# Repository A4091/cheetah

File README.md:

# A4770 Cheetah

A modern successor to the A4091 / A4092.

All the goodness of the A4092:
* TSSOP parts for smaller footprint
* SPI Flash instead of parallel EPROM
* CPLD instead of GALs
* Autoconfig moved into CPLD

And also:
* Update to NCR53c770 SCSI Host Controller
* Ultra-Wide SCSI support
* Drop unneeded ferrites and capacitors on SCSI lines
* Replace DIP-switch mechanism entirely w/ Software/Logic
* No more resistor arrays

# THIS IS WORK IN PROGRESS. DO NOT BUILD. FEEDBACK IS WELCOME

<!-- 

And also as a real PCB:

-->

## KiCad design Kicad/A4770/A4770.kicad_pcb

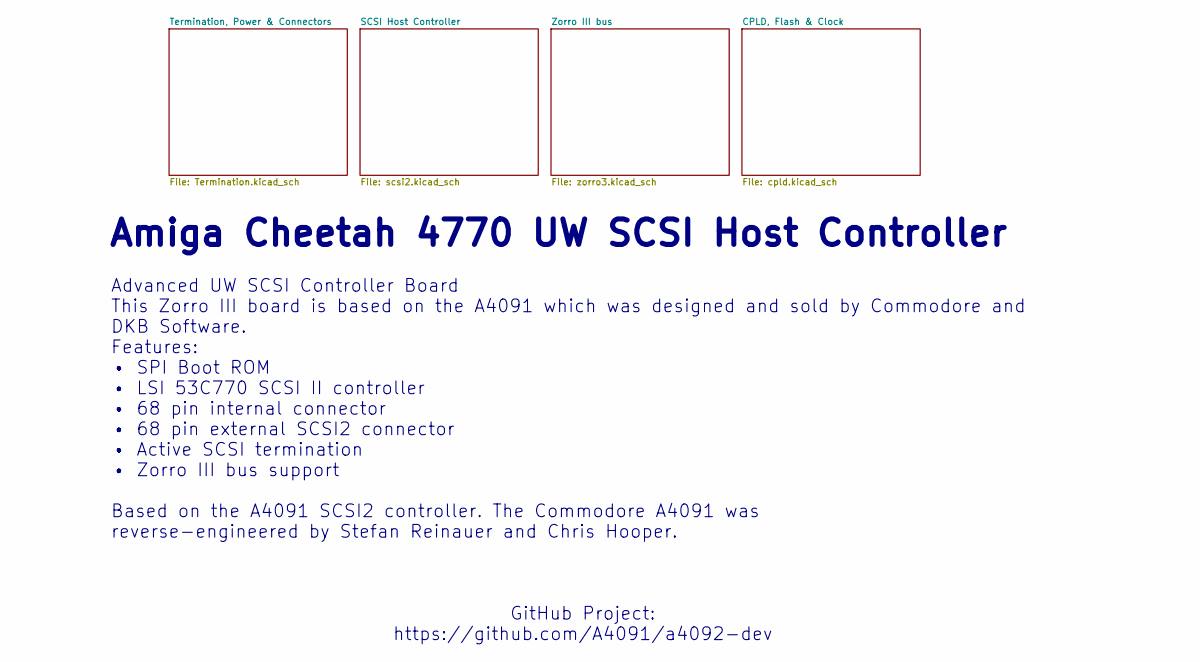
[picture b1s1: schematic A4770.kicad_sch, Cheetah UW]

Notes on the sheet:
Advanced UW SCSI Controller Board This Zorro III board is based on the A4091 which was designed and sold by Commodore and DKB Software. Features: • SPI Boot ROM • LSI 53C770 SCSI II controller • 68 pin internal connector • 68 pin external SCSI2 connector • Active SCSI termination • Zorro III bus su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
GitHub Project: https://github.com/A4091/a4092-dev
Amiga Cheetah 4770 UW SCSI Host Controller

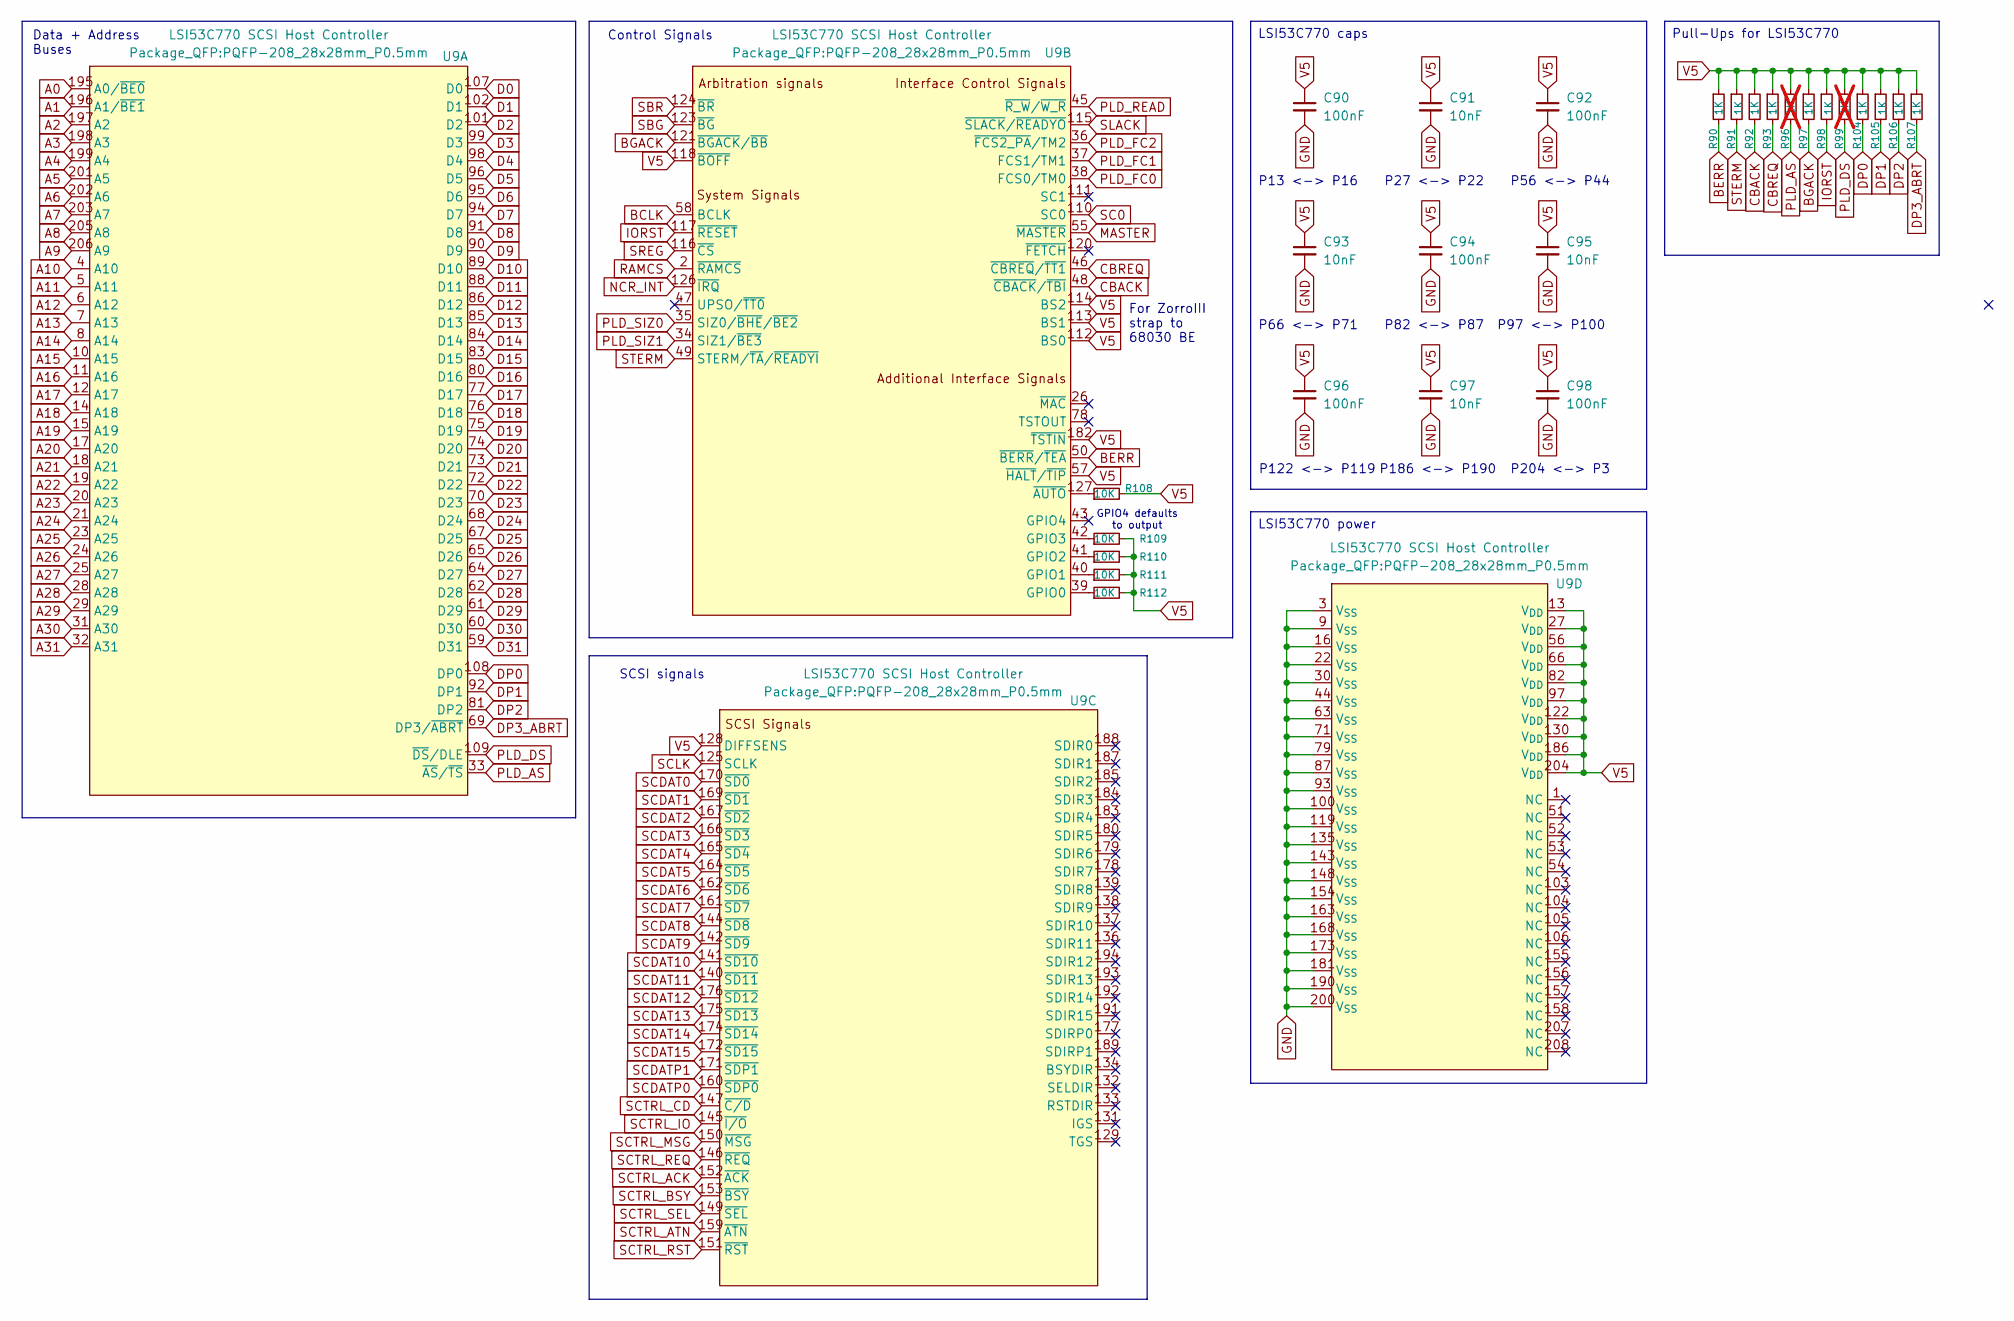
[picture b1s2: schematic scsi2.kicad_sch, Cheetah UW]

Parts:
C90, C92, C94, C96, C98: 100nF; C_0603_1608Metric_Pad1.08x0.95mm_HandSolder; LCSC Part # C14663
C91, C93, C95, C97: 10nF; C_0603_1608Metric_Pad1.08x0.95mm_HandSolder; LCSC Part # C57112
R90, R91, R92, R93, R97, R98, R104, R105, R106, R107: 1K; R_0603_1608Metric_Pad0.98x0.95mm_HandSolder; LCSC Part # C21190
R96, R99: 1K; R_0603_1608Metric_Pad0.98x0.95mm_HandSolder; LCSC Part # C21190; not fitted
R108, R109, R110, R111, R112: 10K; R_0603_1608Metric_Pad0.98x0.95mm_HandSolder; LCSC Part # C25804
U9: LSI53C770 SCSI Host Controller; PQFP-208_28x28mm_P0.5mm; LCSC Part # C9900193416

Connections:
A0: U9.195 (A0/~BE0); also elsewhere on the board
A1: U9.196 (A1/~BE1); also elsewhere on the board
A2: U9.197 (A2); also elsewhere on the board
A3: U9.198 (A3); also elsewhere on the board
A4: U9.199 (A4); also elsewhere on the board
A5: U9.201 (A5); also elsewhere on the board
A6: U9.202 (A6); also elsewhere on the board
A7: U9.203 (A7); also elsewhere on the board
A8: U9.205 (A8); also elsewhere on the board
A9: U9.206 (A9); also elsewhere on the board
A10: U9.4 (A10); also elsewhere on the board
A11: U9.5 (A11); also elsewhere on the board
A12: U9.6 (A12); also elsewhere on the board
A13: U9.7 (A13); also elsewhere on the board
A14: U9.8 (A14); also elsewhere on the board
A15: U9.10 (A15); also elsewhere on the board
A16: U9.11 (A16); also elsewhere on the board
A17: U9.12 (A17); also elsewhere on the board
A18: U9.14 (A18); also elsewhere on the board
A19: U9.15 (A19); also elsewhere on the board
A20: U9.17 (A20); also elsewhere on the board
A21: U9.18 (A21); also elsewhere on the board
A22: U9.19 (A22); also elsewhere on the board
A23: U9.20 (A23); also elsewhere on the board
A24: U9.21 (A24); also elsewhere on the board
A25: U9.23 (A25); also elsewhere on the board
A26: U9.24 (A26); also elsewhere on the board
A27: U9.25 (A27); also elsewhere on the board
A28: U9.28 (A28); also elsewhere on the board
A29: U9.29 (A29); also elsewhere on the board
A30: U9.31 (A30); also elsewhere on the board
A31: U9.32 (A31); also elsewhere on the board
BCLK: U9.58 (BCLK); also elsewhere on the board
BERR: R90.2, U9.50 (~BERR/~TEA); also elsewhere on the board
BGACK: R97.2, U9.121 (~BGACK/~BB)
CBACK: R92.2, U9.48 (~CBACK/~TBI); also elsewhere on the board
CBREQ: R93.2, U9.46 (~CBREQ/~TT1); also elsewhere on the board
D0: U9.107 (D0); also elsewhere on the board
D1: U9.102 (D1); also elsewhere on the board
D2: U9.101 (D2); also elsewhere on the board
D3: U9.99 (D3); also elsewhere on the board
D4: U9.98 (D4); also elsewhere on the board
D5: U9.96 (D5); also elsewhere on the board
D6: U9.95 (D6); also elsewhere on the board
D7: U9.94 (D7); also elsewhere on the board
D8: U9.91 (D8); also elsewhere on the board
D9: U9.90 (D9); also elsewhere on the board
D10: U9.89 (D10); also elsewhere on the board
D11: U9.88 (D11); also elsewhere on the board
D12: U9.86 (D12); also elsewhere on the board
D13: U9.85 (D13); also elsewhere on the board
D14: U9.84 (D14); also elsewhere on the board
D15: U9.83 (D15); also elsewhere on the board
D16: U9.80 (D16); also elsewhere on the board
D17: U9.77 (D17); also elsewhere on the board
D18: U9.76 (D18); also elsewhere on the board
D19: U9.75 (D19); also elsewhere on the board
D20: U9.74 (D20); also elsewhere on the board
D21: U9.73 (D21); also elsewhere on the board
D22: U9.72 (D22); also elsewhere on the board
D23: U9.70 (D23); also elsewhere on the board
D24: U9.68 (D24); also elsewhere on the board
D25: U9.67 (D25); also elsewhere on the board
D26: U9.65 (D26); also elsewhere on the board
D27: U9.64 (D27); also elsewhere on the board
D28: U9.62 (D28); also elsewhere on the board
D29: U9.61 (D29); also elsewhere on the board
D30: U9.60 (D30); also elsewhere on the board
D31: U9.59 (D31); also elsewhere on the board
DP0: R104.2, U9.108 (DP0)
DP1: R105.2, U9.92 (DP1)
DP2: R106.2, U9.81 (DP2)
DP3_ABRT: R107.2, U9.69 (DP3/~ABRT)
GND: C90.2, C91.2, C92.2, C93.2, C94.2, C95.2, C96.2, C97.2, C98.2, U9.3 (V_{SS}), U9.9 (V_{SS}), U9.16 (V_{SS}), U9.22 (V_{SS}), U9.30 (V_{SS}), U9.44 (V_{SS}), U9.63 (V_{SS}), U9.71 (V_{SS}), U9.79 (V_{SS}), U9.87 (V_{SS}), U9.93 (V_{SS}), U9.100 (V_{SS}), U9.119 (V_{SS}), U9.135 (V_{SS}), U9.143 (V_{SS}), U9.148 (V_{SS}), U9.154 (V_{SS}), U9.163 (V_{SS}), U9.168 (V_{SS}), U9.173 (V_{SS}), U9.181 (V_{SS}), U9.190 (V_{SS}), U9.200 (V_{SS}); also elsewhere on the board
IORST: R98.2, U9.117 (~RESET); also elsewhere on the board
MASTER: U9.55 (~MASTER); also elsewhere on the board
NCR_INT: U9.126 (~IRQ); also elsewhere on the board
unnamed: R112.1, U9.39 (GPIO0)
unnamed: R111.1, U9.40 (GPIO1)
unnamed: R110.1, U9.41 (GPIO2)
unnamed: R109.1, U9.42 (GPIO3)
unnamed: R108.1, U9.127 (~AUTO)
PLD_AS: R96.2, U9.33 (~AS/~TS); also elsewhere on the board
PLD_DS: R99.2, U9.109 (~DS/DLE); also elsewhere on the board
PLD_FC0: U9.38 (FCS0/TM0); also elsewhere on the board
PLD_FC1: U9.37 (FCS1/TM1); also elsewhere on the board
PLD_FC2: U9.36 (~FCS2_PA/TM2); also elsewhere on the board
PLD_READ: U9.45 (~R_W/~W_R); also elsewhere on the board
PLD_SIZ0: U9.35 (SIZ0/~BHE/~BE2); also elsewhere on the board
PLD_SIZ1: U9.34 (SIZ1/~BE3); also elsewhere on the board
RAMCS: U9.2 (~RAMCS); also elsewhere on the board
SBG: U9.123 (~BG); also elsewhere on the board
SBR: U9.124 (~BR); also elsewhere on the board
SC0: U9.110 (SC0); also elsewhere on the board
SCDAT0: U9.170 (~SD0); also elsewhere on the board
SCDAT1: U9.169 (~SD1); also elsewhere on the board
SCDAT2: U9.167 (~SD2); also elsewhere on the board
SCDAT3: U9.166 (~SD3); also elsewhere on the board
SCDAT4: U9.165 (~SD4); also elsewhere on the board
SCDAT5: U9.164 (~SD5); also elsewhere on the board
SCDAT6: U9.162 (~SD6); also elsewhere on the board
SCDAT7: U9.161 (~SD7); also elsewhere on the board
SCDAT8: U9.144 (~SD8); also elsewhere on the board
SCDAT9: U9.142 (~SD9); also elsewhere on the board
SCDAT10: U9.141 (~SD10); also elsewhere on the board
SCDAT11: U9.140 (~SD11); also elsewhere on the board
SCDAT12: U9.176 (~SD12); also elsewhere on the board
SCDAT13: U9.175 (~SD13); also elsewhere on the board
SCDAT14: U9.174 (~SD14); also elsewhere on the board
SCDAT15: U9.172 (~SD15); also elsewhere on the board
SCDATP0: U9.160 (~SDP0); also elsewhere on the board
SCDATP1: U9.171 (~SDP1); also elsewhere on the board
SCLK: U9.125 (SCLK); also elsewhere on the board
SCSI_BUSY: U9.153 (~BSY); also elsewhere on the board
SCTRL_ACK: U9.152 (~ACK); also elsewhere on the board
SCTRL_ATN: U9.159 (~ATN); also elsewhere on the board
SCTRL_CD: U9.147 (~C/D); also elsewhere on the board
SCTRL_IO: U9.145 (~I/O); also elsewhere on the board
SCTRL_MSG: U9.150 (~MSG); also elsewhere on the board
SCTRL_REQ: U9.146 (~REQ); also elsewhere on the board
SCTRL_RST: U9.151 (~RST); also elsewhere on the board
SCTRL_SEL: U9.149 (~SEL); also elsewhere on the board
SLACK: U9.115 (~SLACK/~READYO); also elsewhere on the board
SREG: U9.116 (~CS); also elsewhere on the board
STERM: R91.2, U9.49 (STERM/~TA/~READYI); also elsewhere on the board
V5: C90.1, C91.1, C92.1, C93.1, C94.1, C95.1, C96.1, C97.1, C98.1, R90.1, R91.1, R92.1, R93.1, R96.1, R97.1, R98.1, R99.1, R104.1, R105.1, R106.1, R107.1, R108.2, R109.2, R110.2, R111.2, R112.2, U9.13 (V_{DD}), U9.27 (V_{DD}), U9.56 (V_{DD}), U9.57 (~HALT/~TIP), U9.66 (V_{DD}), U9.82 (V_{DD}), U9.97 (V_{DD}), U9.112 (BS0), U9.113 (BS1), U9.114 (BS2), U9.118 (~BOFF), U9.122 (V_{DD}), U9.128 (DIFFSENS), U9.130 (V_{DD}), U9.182 (~TSTIN), U9.186 (V_{DD}), U9.204 (V_{DD}); also elsewhere on the board

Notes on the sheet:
P13 <-> P16
P122 <-> P119
P66 <-> P71
GPIO4 defaults to output
P186 <-> P190
SCSI signals
Control Signals
P204 <-> P3
P56 <-> P44
Data + Address Buses
P82 <-> P87
For ZorroIII strap to 68030 BE
P27 <-> P22
P97 <-> P100
LSI53C770 caps
LSI53C770 power
Pull-Ups for LSI53C770

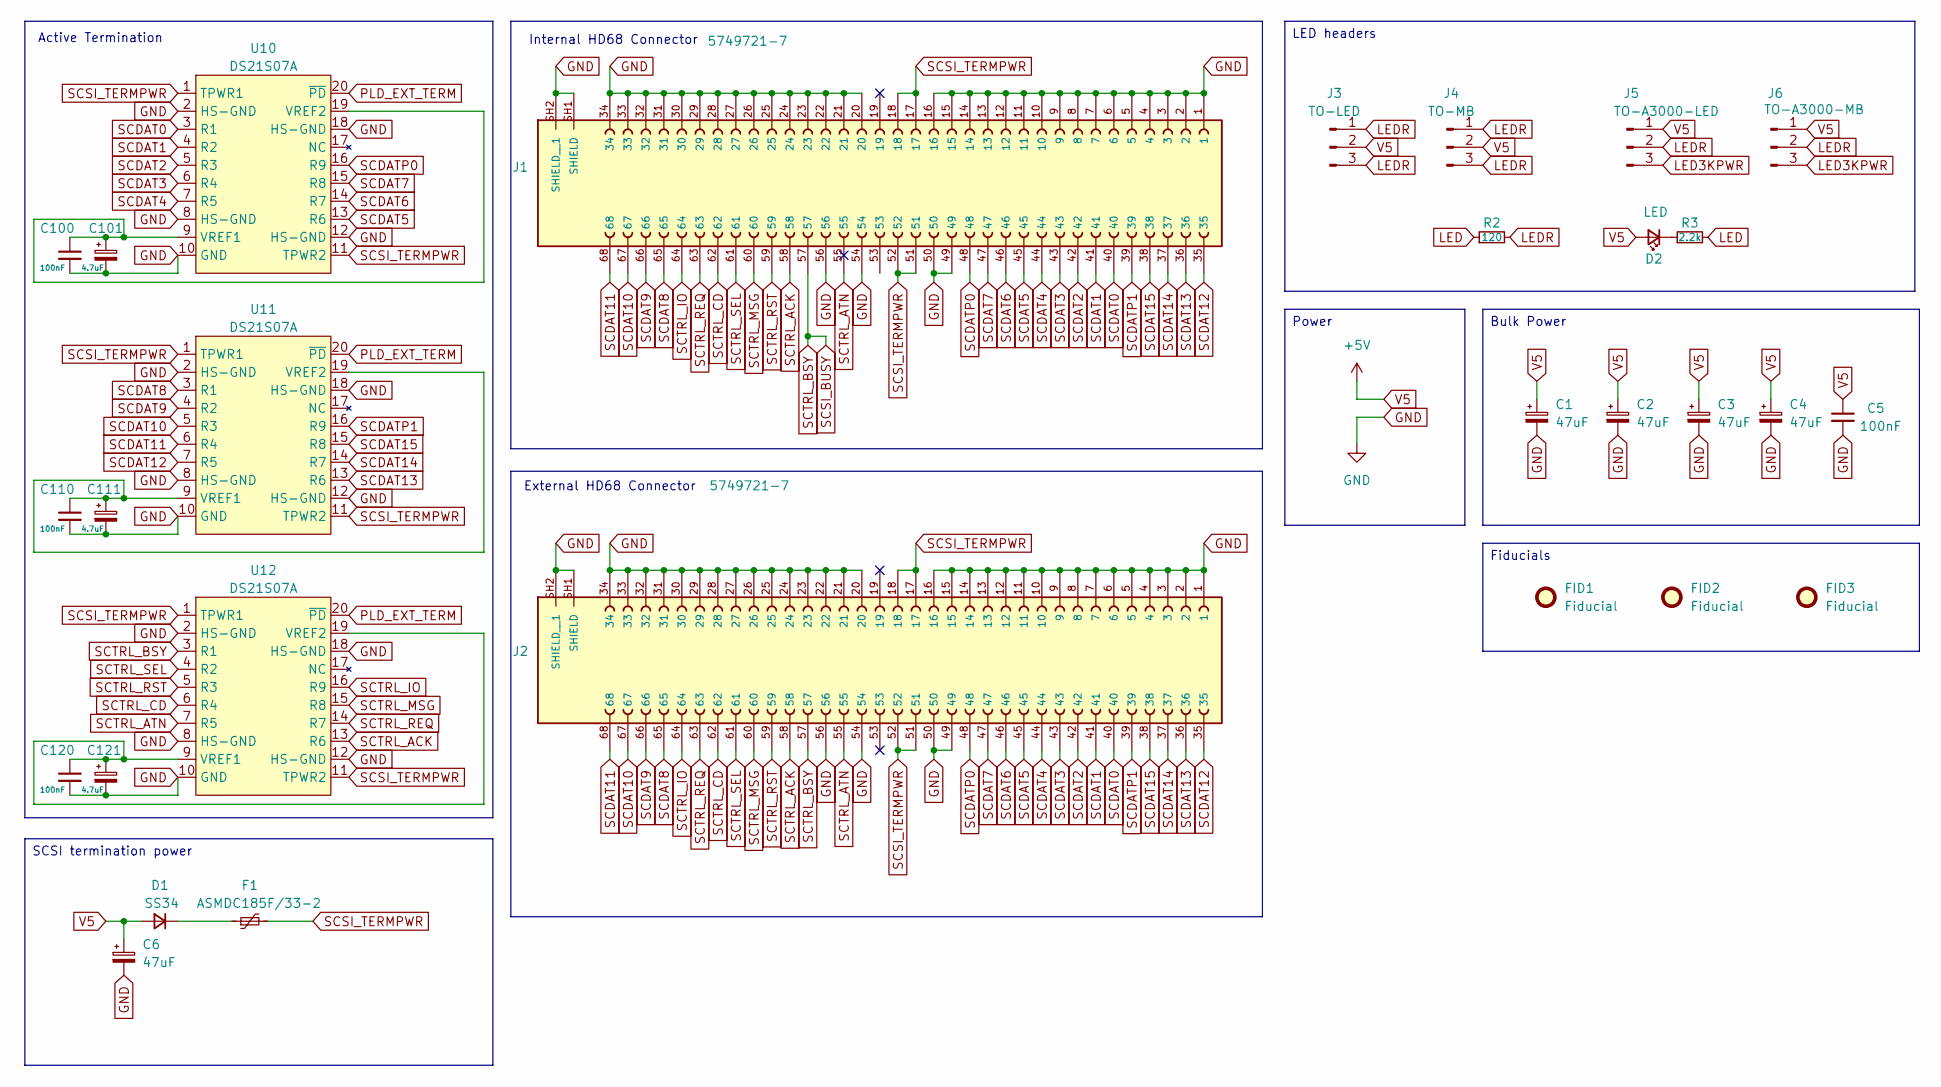
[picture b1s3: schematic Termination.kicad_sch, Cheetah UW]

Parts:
C1, C2, C3, C4, C6: 47uF; CP_Elec_6.3x7.7; MPN KEMET/A765EB476M1ELAE040; LCSC Part # C369909
C5, C100, C110, C120: 100nF; C_0603_1608Metric_Pad1.08x0.95mm_HandSolder; LCSC Part # C14663
C101, C111, C121: 4.7uF; CP_EIA-3216-10_Kemet-I_HandSolder; LCSC Part # C7189
D1: SS34; D_SMA_Handsoldering; LCSC Part # C466483
D2: LED; LED_0805_2012Metric; LCSC Part # C965821
F1: ASMDC185F/33-2; Fuse_2920_7451Metric_Pad2.10x5.45mm_HandSolder; LCSC Part # C780180
FID1, FID2, FID3: Fiducial; Fiducial_0.5mm_Mask1.5mm
J1, J2: 5749721-7; TE_5749721-7; PARTREV B1; LCSC Part # C591675
J3: TO-LED; PinHeader_1x03_P2.54mm_Vertical; LCSC Part # C6332196
J4: TO-MB; PinHeader_1x03_P2.54mm_Vertical; LCSC Part # C6332196
J5: TO-A3000-LED; PinHeader_1x03_P2.54mm_Vertical; LCSC Part # C6332196
J6: TO-A3000-MB; PinHeader_1x03_P2.54mm_Vertical; LCSC Part # C6332196
R2: 120; R_0603_1608Metric; LCSC Part # C22787
R3: 2.2k; R_0603_1608Metric; LCSC Part # C4190
U10, U11, U12: DS21S07A; TSSOP-20_4.4x6.5mm_P0.65mm; LCSC Part # C6602097

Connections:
GND: C1.2, C2.2, C3.2, C4.2, C5.2, C6.2, C100.2, C101.2, C110.2, C111.2, C120.2, C121.2, J1.1, J1.2, J1.3, J1.4, J1.5, J1.6, J1.7, J1.8, J1.9, J1.10, J1.11, J1.12, J1.13, J1.14, J1.15, J1.16, J1.20, J1.21, J1.22, J1.23, J1.24, J1.25, J1.26, J1.27, J1.28, J1.29, J1.30, J1.31, J1.32, J1.33, J1.34, J1.49, J1.50, J1.54, J1.56, J1.SH1 (SHIELD), J1.SH2 (SHIELD__1), J2.1, J2.2, J2.3, J2.4, J2.5, J2.6, J2.7, J2.8, J2.9, J2.10, J2.11, J2.12, J2.13, J2.14, J2.15, J2.16, J2.20, J2.21, J2.22, J2.23, J2.24, J2.25, J2.26, J2.27, J2.28, J2.29, J2.30, J2.31, J2.32, J2.33, J2.34, J2.49, J2.50, J2.54, J2.56, J2.SH1 (SHIELD), J2.SH2 (SHIELD__1), U10.2 (HS-GND), U10.8 (HS-GND), U10.10 (GND), U10.12 (HS-GND), U10.18 (HS-GND), U11.2 (HS-GND), U11.8 (HS-GND), U11.10 (GND), U11.12 (HS-GND), U11.18 (HS-GND), U12.2 (HS-GND), U12.8 (HS-GND), U12.10 (GND), U12.12 (HS-GND), U12.18 (HS-GND); also elsewhere on the board
LED: R2.1, R3.2; also elsewhere on the board
LED3KPWR: J5.3, J6.3
LEDR: J3.1, J3.3, J4.1, J4.3, J5.2, J6.2, R2.2
unnamed: D1.1 (K), F1.1
unnamed: D2.1 (K), R3.1
unnamed: C100.1, C101.1, U10.9 (VREF1), U10.19 (VREF2)
unnamed: C110.1, C111.1, U11.9 (VREF1), U11.19 (VREF2)
unnamed: C120.1, C121.1, U12.9 (VREF1), U12.19 (VREF2)
PLD_EXT_TERM: U10.20 (~PD), U11.20 (~PD), U12.20 (~PD); also elsewhere on the board
SCDAT0: J1.40, J2.40, U10.3 (R1); also elsewhere on the board
SCDAT1: J1.41, J2.41, U10.4 (R2); also elsewhere on the board
SCDAT2: J1.42, J2.42, U10.5 (R3); also elsewhere on the board
SCDAT3: J1.43, J2.43, U10.6 (R4); also elsewhere on the board
SCDAT4: J1.44, J2.44, U10.7 (R5); also elsewhere on the board
SCDAT5: J1.45, J2.45, U10.13 (R6); also elsewhere on the board
SCDAT6: J1.46, J2.46, U10.14 (R7); also elsewhere on the board
SCDAT7: J1.47, J2.47, U10.15 (R8); also elsewhere on the board
SCDAT8: J1.65, J2.65, U11.3 (R1); also elsewhere on the board
SCDAT9: J1.66, J2.66, U11.4 (R2); also elsewhere on the board
SCDAT10: J1.67, J2.67, U11.5 (R3); also elsewhere on the board
SCDAT11: J1.68, J2.68, U11.6 (R4); also elsewhere on the board
SCDAT12: J1.35, J2.35, U11.7 (R5); also elsewhere on the board
SCDAT13: J1.36, J2.36, U11.13 (R6); also elsewhere on the board
SCDAT14: J1.37, J2.37, U11.14 (R7); also elsewhere on the board
SCDAT15: J1.38, J2.38, U11.15 (R8); also elsewhere on the board
SCDATP0: J1.48, J2.48, U10.16 (R9); also elsewhere on the board
SCDATP1: J1.39, J2.39, U11.16 (R9); also elsewhere on the board
SCSI_BUSY: J1.57, J2.57, U12.3 (R1); also elsewhere on the board
SCSI_TERMPWR: F1.2, J1.17, J1.18, J1.51, J1.52, J2.17, J2.18, J2.51, J2.52, U10.1 (TPWR1), U10.11 (TPWR2), U11.1 (TPWR1), U11.11 (TPWR2), U12.1 (TPWR1), U12.11 (TPWR2)
SCTRL_ACK: J1.58, J2.58, U12.13 (R6); also elsewhere on the board
SCTRL_ATN: J1.55, J2.55, U12.7 (R5); also elsewhere on the board
SCTRL_CD: J1.62, J2.62, U12.6 (R4); also elsewhere on the board
SCTRL_IO: J1.64, J2.64, U12.16 (R9); also elsewhere on the board
SCTRL_MSG: J1.60, J2.60, U12.15 (R8); also elsewhere on the board
SCTRL_REQ: J1.63, J2.63, U12.14 (R7); also elsewhere on the board
SCTRL_RST: J1.59, J2.59, U12.5 (R3); also elsewhere on the board
SCTRL_SEL: J1.61, J2.61, U12.4 (R2); also elsewhere on the board
V5: C1.1, C2.1, C3.1, C4.1, C5.1, C6.1, D1.2 (A), D2.2 (A), J3.2, J4.2, J5.1, J6.1; also elsewhere on the board

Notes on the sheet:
Active Termination
Internal HD68 Connector
External HD68 Connector
SCSI termination power
Fiducials
Power
LED headers
Bulk Power

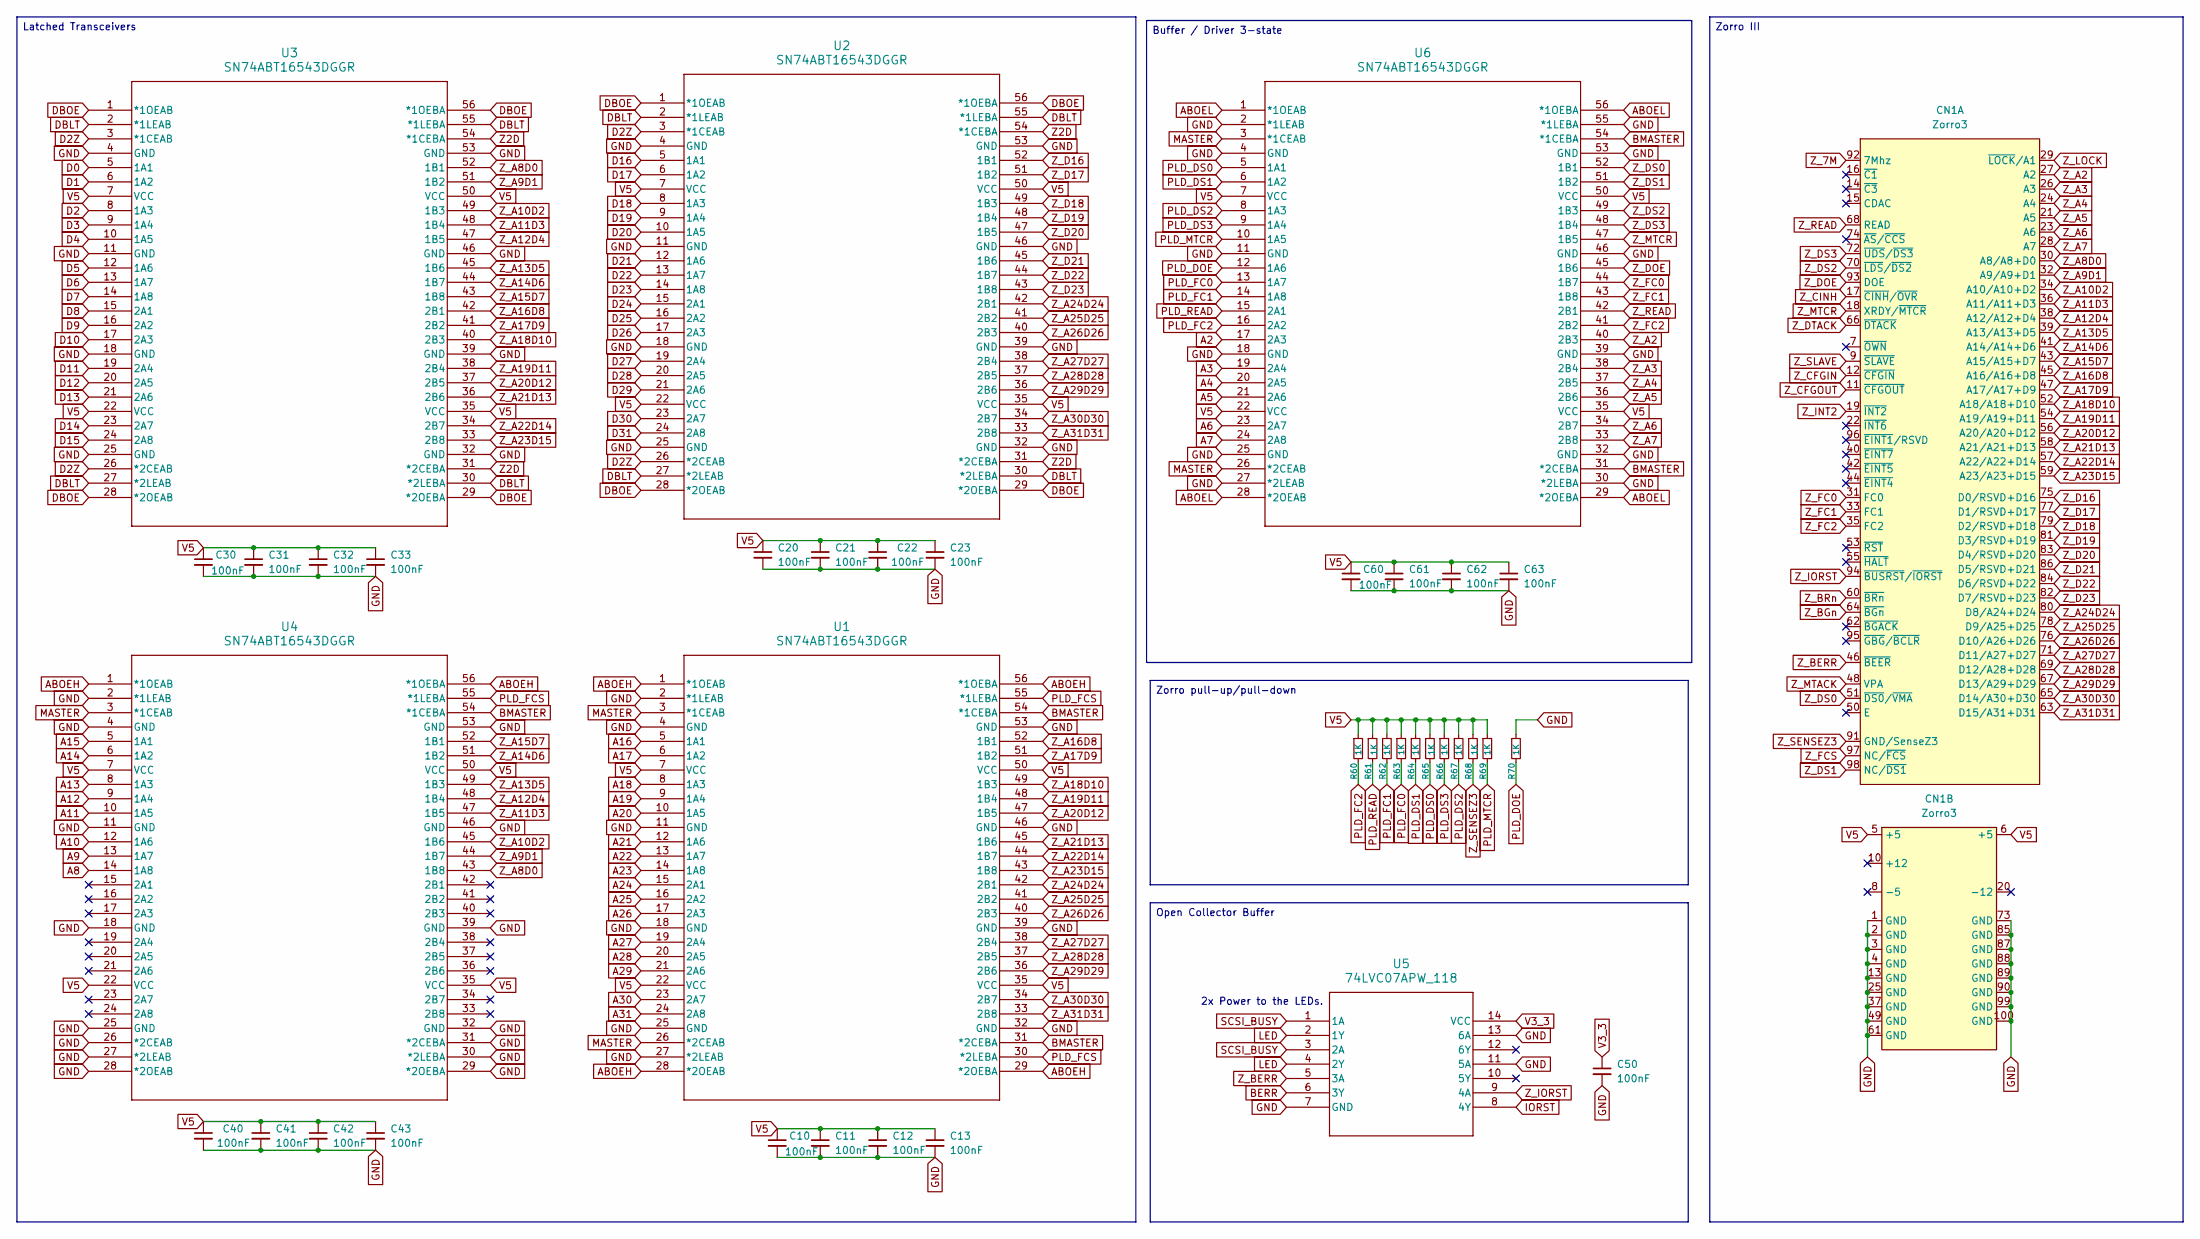
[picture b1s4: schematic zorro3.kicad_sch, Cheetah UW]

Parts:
C10, C11, C12, C13, C20, C21, C22, C23, C30, C31, C32, C33, C40, C41, C42, C43, C50, C60, C61, C62, C63: 100nF; C_0603_1608Metric_Pad1.08x0.95mm_HandSolder; LCSC Part # C14663
CN1: Zorro3; Zorro3-CardEdge
R60, R61, R62, R63, R64, R65, R66, R67, R68, R69, R70: 1K; R_0603_1608Metric_Pad0.98x0.95mm_HandSolder; LCSC Part # C21190
U1, U2, U3, U4, U6: SN74ABT16543DGGR; DGG56; LCSC Part # C2865087
U5: 74LVC07APW_118; TSSOP14_5P1X4P5_NEX; LCSC Part # C6051

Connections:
A2: U6.17 (2A3); also elsewhere on the board
A3: U6.19 (2A4); also elsewhere on the board
A4: U6.20 (2A5); also elsewhere on the board
A5: U6.21 (2A6); also elsewhere on the board
A6: U6.23 (2A7); also elsewhere on the board
A7: U6.24 (2A8); also elsewhere on the board
A8: U4.14 (1A8); also elsewhere on the board
A9: U4.13 (1A7); also elsewhere on the board
A10: U4.12 (1A6); also elsewhere on the board
A11: U4.10 (1A5); also elsewhere on the board
A12: U4.9 (1A4); also elsewhere on the board
A13: U4.8 (1A3); also elsewhere on the board
A14: U4.6 (1A2); also elsewhere on the board
A15: U4.5 (1A1); also elsewhere on the board
A16: U1.5 (1A1); also elsewhere on the board
A17: U1.6 (1A2); also elsewhere on the board
A18: U1.8 (1A3); also elsewhere on the board
A19: U1.9 (1A4); also elsewhere on the board
A20: U1.10 (1A5); also elsewhere on the board
A21: U1.12 (1A6); also elsewhere on the board
A22: U1.13 (1A7); also elsewhere on the board
A23: U1.14 (1A8); also elsewhere on the board
A24: U1.15 (2A1); also elsewhere on the board
A25: U1.16 (2A2); also elsewhere on the board
A26: U1.17 (2A3); also elsewhere on the board
A27: U1.19 (2A4); also elsewhere on the board
A28: U1.20 (2A5); also elsewhere on the board
A29: U1.21 (2A6); also elsewhere on the board
A30: U1.23 (2A7); also elsewhere on the board
A31: U1.24 (2A8); also elsewhere on the board
ABOEH: U1.1 (*1OEAB), U1.28 (*2OEAB), U1.29 (*2OEBA), U1.56 (*1OEBA), U4.1 (*1OEAB), U4.56 (*1OEBA); also elsewhere on the board
ABOEL: U6.1 (*1OEAB), U6.28 (*2OEAB), U6.29 (*2OEBA), U6.56 (*1OEBA); also elsewhere on the board
BERR: U5.6 (3Y); also elsewhere on the board
BMASTER: U1.31 (*2CEBA), U1.54 (*1CEBA), U4.54 (*1CEBA), U6.31 (*2CEBA), U6.54 (*1CEBA); also elsewhere on the board
D0: U3.5 (1A1); also elsewhere on the board
D1: U3.6 (1A2); also elsewhere on the board
D2: U3.8 (1A3); also elsewhere on the board
D2Z: U2.3 (*1CEAB), U2.26 (*2CEAB), U3.3 (*1CEAB), U3.26 (*2CEAB); also elsewhere on the board
D3: U3.9 (1A4); also elsewhere on the board
D4: U3.10 (1A5); also elsewhere on the board
D5: U3.12 (1A6); also elsewhere on the board
D6: U3.13 (1A7); also elsewhere on the board
D7: U3.14 (1A8); also elsewhere on the board
D8: U3.15 (2A1); also elsewhere on the board
D9: U3.16 (2A2); also elsewhere on the board
D10: U3.17 (2A3); also elsewhere on the board
D11: U3.19 (2A4); also elsewhere on the board
D12: U3.20 (2A5); also elsewhere on the board
D13: U3.21 (2A6); also elsewhere on the board
D14: U3.23 (2A7); also elsewhere on the board
D15: U3.24 (2A8); also elsewhere on the board
D16: U2.5 (1A1); also elsewhere on the board
D17: U2.6 (1A2); also elsewhere on the board
D18: U2.8 (1A3); also elsewhere on the board
D19: U2.9 (1A4); also elsewhere on the board
D20: U2.10 (1A5); also elsewhere on the board
D21: U2.12 (1A6); also elsewhere on the board
D22: U2.13 (1A7); also elsewhere on the board
D23: U2.14 (1A8); also elsewhere on the board
D24: U2.15 (2A1); also elsewhere on the board
D25: U2.16 (2A2); also elsewhere on the board
D26: U2.17 (2A3); also elsewhere on the board
D27: U2.19 (2A4); also elsewhere on the board
D28: U2.20 (2A5); also elsewhere on the board
D29: U2.21 (2A6); also elsewhere on the board
D30: U2.23 (2A7); also elsewhere on the board
D31: U2.24 (2A8); also elsewhere on the board
DBLT: U2.2 (*1LEAB), U2.27 (*2LEAB), U2.30 (*2LEBA), U2.55 (*1LEBA), U3.2 (*1LEAB), U3.27 (*2LEAB), U3.30 (*2LEBA), U3.55 (*1LEBA); also elsewhere on the board
DBOE: U2.1 (*1OEAB), U2.28 (*2OEAB), U2.29 (*2OEBA), U2.56 (*1OEBA), U3.1 (*1OEAB), U3.28 (*2OEAB), U3.29 (*2OEBA), U3.56 (*1OEBA); also elsewhere on the board
GND: C10.2, C11.2, C12.2, C13.2, C20.2, C21.2, C22.2, C23.2, C30.2, C31.2, C32.2, C33.2, C40.2, C41.2, C42.2, C43.2, C50.2, C60.2, C61.2, C62.2, C63.2, CN1.1 (GND), CN1.2 (GND), CN1.3 (GND), CN1.4 (GND), CN1.13 (GND), CN1.25 (GND), CN1.37 (GND), CN1.49 (GND), CN1.61 (GND), CN1.73 (GND), CN1.85 (GND), CN1.87 (GND), CN1.88 (GND), CN1.89 (GND), CN1.90 (GND), CN1.99 (GND), CN1.100 (GND), R70.1, U1.2 (*1LEAB), U1.4 (GND), U1.11 (GND), U1.18 (GND), U1.25 (GND), U1.27 (*2LEAB), U1.32 (GND), U1.39 (GND), U1.46 (GND), U1.53 (GND), U2.4 (GND), U2.11 (GND), U2.18 (GND), U2.25 (GND), U2.32 (GND), U2.39 (GND), U2.46 (GND), U2.53 (GND), U3.4 (GND), U3.11 (GND), U3.18 (GND), U3.25 (GND), U3.32 (GND), U3.39 (GND), U3.46 (GND), U3.53 (GND), U4.2 (*1LEAB), U4.4 (GND), U4.11 (GND), U4.18 (GND), U4.25 (GND), U4.26 (*2CEAB), U4.27 (*2LEAB), U4.28 (*2OEAB), U4.29 (*2OEBA), U4.30 (*2LEBA), U4.31 (*2CEBA), U4.32 (GND), U4.39 (GND), U4.46 (GND), U4.53 (GND), U5.7 (GND), U5.11 (5A), U5.13 (6A), U6.2 (*1LEAB), U6.4 (GND), U6.11 (GND), U6.18 (GND), U6.25 (GND), U6.27 (*2LEAB), U6.30 (*2LEBA), U6.32 (GND), U6.39 (GND), U6.46 (GND), U6.53 (GND), U6.55 (*1LEBA); also elsewhere on the board
IORST: U5.8 (4Y); also elsewhere on the board
LED: U5.2 (1Y), U5.4 (2Y); also elsewhere on the board
MASTER: U1.3 (*1CEAB), U1.26 (*2CEAB), U4.3 (*1CEAB), U6.3 (*1CEAB), U6.26 (*2CEAB); also elsewhere on the board
PLD_DOE: R70.2, U6.12 (1A6); also elsewhere on the board
PLD_DS0: R65.2, U6.5 (1A1); also elsewhere on the board
PLD_DS1: R64.2, U6.6 (1A2); also elsewhere on the board
PLD_DS2: R67.2, U6.8 (1A3); also elsewhere on the board
PLD_DS3: R66.2, U6.9 (1A4); also elsewhere on the board
PLD_FC0: R63.2, U6.13 (1A7); also elsewhere on the board
PLD_FC1: R62.2, U6.14 (1A8); also elsewhere on the board
PLD_FC2: R60.2, U6.16 (2A2); also elsewhere on the board
PLD_FCS: U1.30 (*2LEBA), U1.55 (*1LEBA), U4.55 (*1LEBA); also elsewhere on the board
PLD_MTCR: R69.2, U6.10 (1A5); also elsewhere on the board
PLD_READ: R61.2, U6.15 (2A1); also elsewhere on the board
SCSI_BUSY: U5.1 (1A), U5.3 (2A); also elsewhere on the board
V3_3: C50.1, U5.14 (VCC); also elsewhere on the board
V5: C10.1, C11.1, C12.1, C13.1, C20.1, C21.1, C22.1, C23.1, C30.1, C31.1, C32.1, C33.1, C40.1, C41.1, C42.1, C43.1, C60.1, C61.1, C62.1, C63.1, CN1.5 (+5), CN1.6 (+5), R60.1, R61.1, R62.1, R63.1, R64.1, R65.1, R66.1, R67.1, R68.1, R69.1, U1.7 (VCC), U1.22 (VCC), U1.35 (VCC), U1.50 (VCC), U2.7 (VCC), U2.22 (VCC), U2.35 (VCC), U2.50 (VCC), U3.7 (VCC), U3.22 (VCC), U3.35 (VCC), U3.50 (VCC), U4.7 (VCC), U4.22 (VCC), U4.35 (VCC), U4.50 (VCC), U6.7 (VCC), U6.22 (VCC), U6.35 (VCC), U6.50 (VCC); also elsewhere on the board
Z2D: U2.31 (*2CEBA), U2.54 (*1CEBA), U3.31 (*2CEBA), U3.54 (*1CEBA); also elsewhere on the board
Z_7M: CN1.92 (7Mhz); also elsewhere on the board
Z_A2: CN1.27 (A2), U6.40 (2B3)
Z_A3: CN1.26 (A3), U6.38 (2B4)
Z_A4: CN1.24 (A4), U6.37 (2B5)
Z_A5: CN1.21 (A5), U6.36 (2B6)
Z_A6: CN1.23 (A6), U6.34 (2B7)
Z_A7: CN1.28 (A7), U6.33 (2B8)
Z_A8D0: CN1.30 (A8/A8+D0), U3.52 (1B1), U4.43 (1B8)
Z_A9D1: CN1.32 (A9/A9+D1), U3.51 (1B2), U4.44 (1B7)
Z_A10D2: CN1.34 (A10/A10+D2), U3.49 (1B3), U4.45 (1B6)
Z_A11D3: CN1.36 (A11/A11+D3), U3.48 (1B4), U4.47 (1B5)
Z_A12D4: CN1.38 (A12/A12+D4), U3.47 (1B5), U4.48 (1B4)
Z_A13D5: CN1.39 (A13/A13+D5), U3.45 (1B6), U4.49 (1B3)
Z_A14D6: CN1.41 (A14/A14+D6), U3.44 (1B7), U4.51 (1B2)
Z_A15D7: CN1.43 (A15/A15+D7), U3.43 (1B8), U4.52 (1B1)
Z_A16D8: CN1.45 (A16/A16+D8), U1.52 (1B1), U3.42 (2B1)
Z_A17D9: CN1.47 (A17/A17+D9), U1.51 (1B2), U3.41 (2B2)
Z_A18D10: CN1.52 (A18/A18+D10), U1.49 (1B3), U3.40 (2B3)
Z_A19D11: CN1.54 (A19/A19+D11), U1.48 (1B4), U3.38 (2B4)
Z_A20D12: CN1.56 (A20/A20+D12), U1.47 (1B5), U3.37 (2B5)
Z_A21D13: CN1.58 (A21/A21+D13), U1.45 (1B6), U3.36 (2B6)
Z_A22D14: CN1.57 (A22/A22+D14), U1.44 (1B7), U3.34 (2B7)
Z_A23D15: CN1.59 (A23/A23+D15), U1.43 (1B8), U3.33 (2B8)
Z_A24D24: CN1.80 (D8/A24+D24), U1.42 (2B1), U2.42 (2B1)
Z_A25D25: CN1.78 (D9/A25+D25), U1.41 (2B2), U2.41 (2B2)
Z_A26D26: CN1.76 (D10/A26+D26), U1.40 (2B3), U2.40 (2B3)
Z_A27D27: CN1.71 (D11/A27+D27), U1.38 (2B4), U2.38 (2B4)
Z_A28D28: CN1.69 (D12/A28+D28), U1.37 (2B5), U2.37 (2B5)
Z_A29D29: CN1.67 (D13/A29+D29), U1.36 (2B6), U2.36 (2B6)
Z_A30D30: CN1.65 (D14/A30+D30), U1.34 (2B7), U2.34 (2B7)
Z_A31D31: CN1.63 (D15/A31+D31), U1.33 (2B8), U2.33 (2B8)
Z_BERR: CN1.46 (~BEER), U5.5 (3A)
Z_BGn: CN1.64 (~BGn); also elsewhere on the board
Z_BRn: CN1.60 (~BRn); also elsewhere on the board
Z_CFGIN: CN1.12 (~CFGIN); also elsewhere on the board
Z_CFGOUT: CN1.11 (~CFGOUT); also elsewhere on the board
Z_CINH: CN1.17 (~CINH/~OVR); also elsewhere on the board
Z_D16: CN1.75 (D0/RSVD+D16), U2.52 (1B1)
Z_D17: CN1.77 (D1/RSVD+D17), U2.51 (1B2)
Z_D18: CN1.79 (D2/RSVD+D18), U2.49 (1B3)
Z_D19: CN1.81 (D3/RSVD+D19), U2.48 (1B4)
Z_D20: CN1.83 (D4/RSVD+D20), U2.47 (1B5)
Z_D21: CN1.86 (D5/RSVD+D21), U2.45 (1B6)
Z_D22: CN1.84 (D6/RSVD+D22), U2.44 (1B7)
Z_D23: CN1.82 (D7/RSVD+D23), U2.43 (1B8)
Z_DOE: CN1.93 (DOE), U6.45 (1B6)
Z_DS0: CN1.51 (~DS0/~VMA), U6.52 (1B1)
Z_DS1: CN1.98 (NC/~DS1), U6.51 (1B2)
Z_DS2: CN1.70 (~LDS/~DS2), U6.49 (1B3)
Z_DS3: CN1.72 (~UDS/~DS3), U6.48 (1B4)
Z_DTACK: CN1.66 (~DTACK); also elsewhere on the board
Z_FC0: CN1.31 (FC0), U6.44 (1B7)
Z_FC1: CN1.33 (FC1), U6.43 (1B8)
Z_FC2: CN1.35 (FC2), U6.41 (2B2)
Z_FCS: CN1.97 (NC/~FCS); also elsewhere on the board
Z_INT2: CN1.19 (~INT2); also elsewhere on the board
Z_IORST: CN1.94 (~BUSRST/~IORST), U5.9 (4A)
Z_LOCK: CN1.29 (~LOCK/A1); also elsewhere on the board
Z_MTACK: CN1.48 (VPA); also elsewhere on the board
Z_MTCR: CN1.18 (XRDY/~MTCR), U6.47 (1B5)
Z_READ: CN1.68 (READ), U6.42 (2B1)
Z_SENSEZ3: CN1.91 (GND/SenseZ3), R68.2; also elsewhere on the board
Z_SLAVE: CN1.9 (~SLAVE); also elsewhere on the board

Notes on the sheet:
2x Power to the LEDs.
Buffer / Driver 3-state
Zorro pull-up/pull-down
Latched Transceivers
Open Collector Buffer
Zorro III
